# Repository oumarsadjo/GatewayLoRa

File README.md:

# SUIVI COMPLET DU PROJET -> GatewayLoRa
- Annee: 2023-2024
- Projet: GetwayLoRa
- Niveau: 4 annee
- Ecole: Polytch Nice Sophia
- Eleves: Oumar Sadjo Barry & Mor Djeng / oumar-sadjo.barry@etu.univ-cotedazur.fr & mor.dieng@etu.univ-cotedazur.fr
- Professeur: Monsieur Christian Peter / christian.peter@univ-cotedazur.fr
- Derniere mise a jour: _Lundi 05 Fevrier 2024_          

## LES ETAPES QUE NOUS AVONS SUIVI SONT

_1. LECTURES DES DIFFERENTES DOCUMENTATIONS
------------------------------------------
Nous avons commencé par lire attentivement toutes les documents (datasheets),
des deux cartes. C'est qui nous a donne une vue générale de leurs fonctionnements.
Nous avons analysé les differents schematics et prendre connaissance de leur brochages.

_2. INTERCONNEXION DES DEUX CARTES (CABLAGE)
------------------------------------------
Apres avoir pris connaissance des deux datasheet, nous avons choisi un protocole de
communication UART pour permettre la transmission. Nous avons identifié l'alimentation
des deux cartes qui à 5V chacune.

_3. PROTOCOLE ET BROCHAGE
------------------------
- Protocole: UART
- Connexion:
- ESP32 (ports) vers SIM7000G (ports)
- 5V    ------------> V
- GND   ------------> G
- 16    ------------> T //RX to TX
- 17    ------------> R //TX to RX

_4. UTILISATION DE IDE ARDUINO POUR LES TESTS
--------------------------------------------
Nous avons codé une première fonction "void sendCommand(String myCommand)", qui permet
d'envoyer des commandes AT et afficher le resultat au port serial désiré.
NOTE: Toutes les fonctions sont ecrites dans un fichier d'entete (header), nomme "myFonctions.h".

_5. LES PREMIERES FONCTIONS
-------------------------
Nous avons ecris une premiere fonction capable d'envoyer un SMS a un numero désiré nommee : 
"void sendMessage(const char* numero, const char* texte)" et une deuxième fonction qui permet de lire
des messages recus nommee: "void readMessage()".

_6. FONCTIONS PRINCIPALES
------------------------
- A. void myWiFiConnexion(const char* ssid, const char* password): cette fonction nous permet de se connecter un reseau WiFi desire.

- B. void sendRequestByWiFi(const char* ssid, const char* password, const String urlServer):
   Cette fonction permet d'envoyer des requettes HTTP GET en utilisant un reseau WiFi dedié. La limite de cette foncttionnalité,
   est que certains endroits où se projet sera utilisé; n'ont pas de WiFi. Pour aller plus loin, on va utiliser le GSM.
  Elle procede comme suit:
  - a. Connexion a un reseau WiFi
  - b. Verification de la connexion
  - c. Initialisation du protocole HTTP
  - d. Obtention de la longeur ou de la taille de la page
  - e. Affichage du resultat obtenu
  - f. Fermeture du protocole HTTP
    
- C. void sendRequestByGSM(const char* url):
   Cette fonction permet d'envoyer des requettes HTTP GET en utilisant le reseau GSM. L'utilisateur precise le serveur ou le lien.
   Elle procede comme suit:
  - a. Initialisation du reseau GSM
  - b. Obtention d'une IP adress pour communiquer en GSM
  - c. Initialisation du protocole HTTP
  - d. Obtention de la longeur ou de la taille de la page
  - e. Affichage du resultat obtenu
  - f. Fermeture du protocole HTTP

_7. ETAPES SCHEMATICS
--------------------
Pour cette etape de Design, nous avons choisi l'ensemble des composants et voir leur disponibilite sur le site du sous-traitant.
Le design a ete valide par notre professeur. Nous avons constitue le BOM et l'envoye au professeur pour commander les composants.
Nous allons maintenant passer a l'etape de routage.

Lors de la seance du 13 Fevrier 2024, nous avons apporter des corrections au schematic et ajouter le convertisseur TXB0108PWR
pour connecter les tensions de +1V8.

_8. ETAPES ROUTAGE
--------------------
Comme le design a ete valide et les materiels sont disponible, nous allons maintenant continuer le routage...
A continuer lors de la prochaine seance : _Mardi 18 Fevrier 2024_

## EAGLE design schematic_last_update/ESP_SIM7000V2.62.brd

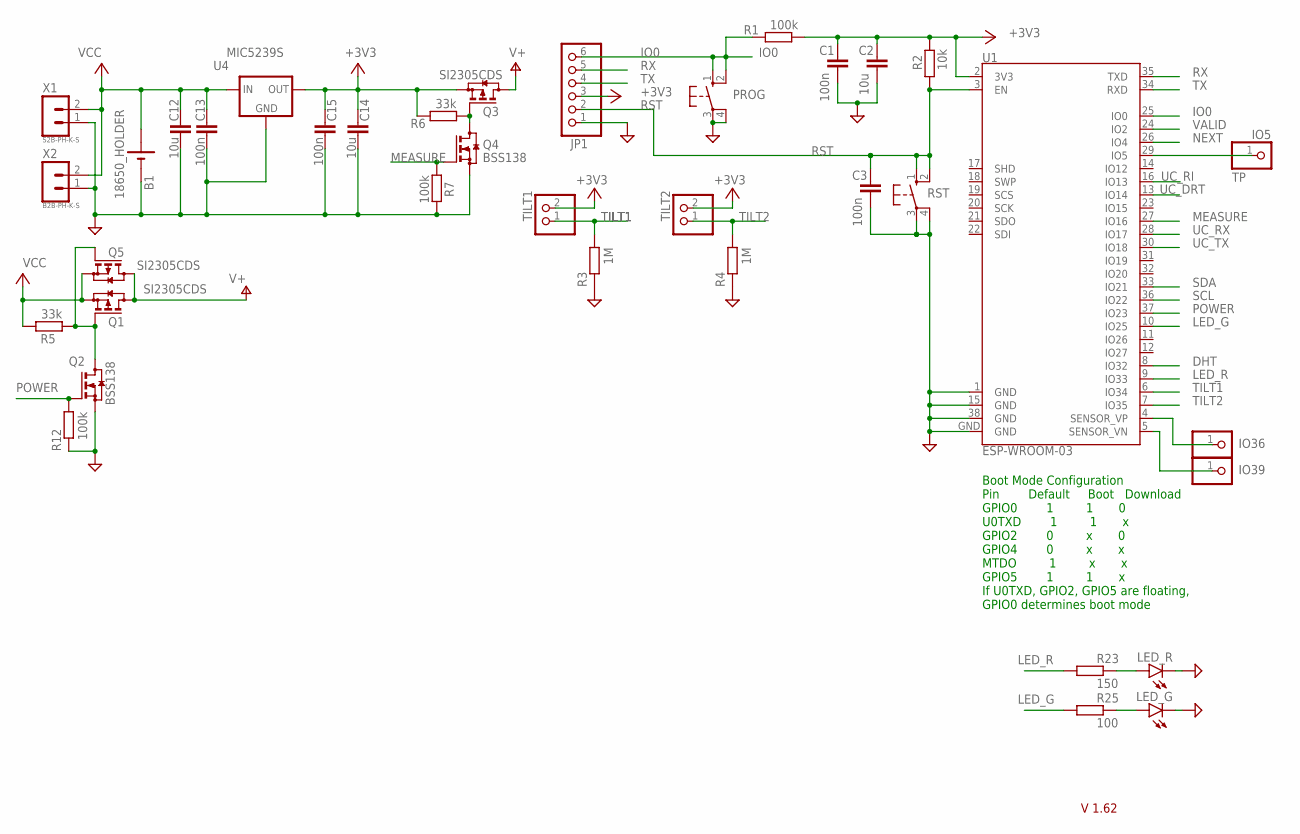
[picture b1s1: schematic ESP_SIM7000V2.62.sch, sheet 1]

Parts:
B1: 18650_HOLDER; 18650
C1, C3, C13, C15: 100n; C1206
C2, C12, C14: 10u; C1210
IO5: TP; 1X01
IO36, IO39: PINHD-1X1; 1X01
JP1: PINHD-1X6; 1X06
LED_G: LEDSMT1206; 1206
LED_R: LEDSMT1206; 1206
PROG: 10-XX; B3F-10XX
Q1, Q3, Q5: SI2305CDS; SOT23
Q2, Q4: BSS138; SOT23
R1, R7, R12: 100k; R1206
R2: 10k; R1206
R3, R4: 1M; R1206
R5, R6: 33k; R1206
R23: 150; R1206
R25: 100; R1206
RST: 10-XX; B3F-10XX
TILT1, TILT2: PINHD-1X2; 1X02
U1: ESP-WROOM-03
U4: MIC5239S; SOT223
X1: S2B-PH-K-S
X2: B2B-PH-K-S

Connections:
+3V3: C1.1, C2.1, C14.1, C15.1, JP1.3, Q3.2 (S), R1.1, R2.2, R6.2, TILT1.2, TILT2.2, U1.2 (3V3), U4.3 (OUT); also elsewhere on the board
DHT: U1.8 (IO32)
GND: B1.-, C1.2, C2.2, C3.2, C12.2, C13.2, C14.2, C15.2, JP1.1, LED_G.C, LED_R.C, PROG.3, PROG.4 (P1), Q2.2 (S), Q4.2 (S), R3.2, R4.2, R7.2, R12.2, RST.3, RST.4 (P1), U1.1 (GND), U1.15 (GND), U1.38 (GND), U1.GND, U4.2 (GND), U4.4 (GND), X1.1, X2.1; also elsewhere on the board
IO0: JP1.6, PROG.1 (S), PROG.2 (S1), R1.2, U1.25 (IO0)
IO36: IO36.1, U1.4 (SENSOR_VP)
IO39: IO39.1, U1.5 (SENSOR_VN)
LED_G: R25.1, U1.10 (IO25)
LED_R: R23.1, U1.9 (IO33); also elsewhere on the board
MEASURE: Q4.1 (G), R7.1, U1.27 (IO16)
unnamed: Q1.1 (G), Q2.3 (D), Q5.1 (G), R5.1
unnamed: Q3.1 (G), Q4.3 (D), R6.1
unnamed: LED_R.A, R23.2
unnamed: LED_G.A, R25.2
unnamed: IO5.1, U1.29 (IO5)
NEXT: U1.26 (IO4)
POWER: Q2.1 (G), R12.1, U1.37 (IO23)
RST: C3.1, JP1.2, R2.1, RST.1 (S), RST.2 (S1), U1.3 (EN)
RX: JP1.5, U1.35 (TXD)
SCL: U1.36 (IO22); also elsewhere on the board
SDA: U1.33 (IO21); also elsewhere on the board
TILT1: R3.1, TILT1.1, U1.6 (IO34)
TILT2: R4.1, TILT2.1, U1.7 (IO35)
TX: JP1.4, U1.34 (RXD)
UC_DRT: U1.13 (IO14); also elsewhere on the board
UC_RI: U1.16 (IO13); also elsewhere on the board
UC_RX: U1.28 (IO17); also elsewhere on the board
UC_TX: U1.30 (IO18); also elsewhere on the board
V+: Q1.3 (D), Q3.3 (D), Q5.3 (D); also elsewhere on the board
VALID: U1.24 (IO2)
VCC: B1.+, C12.1, C13.1, Q1.2 (S), Q5.2 (S), R5.2, U4.1 (IN), X1.2, X2.2

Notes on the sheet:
Boot Mode Configuration Pin Default Boot Download GPIO0 1 1 0 U0TXD 1 1 x GPIO2 0 x 0 GPIO4 0 x x MTDO 1 x x GPIO5 1 1 x If U0TXD, GPIO2, GPIO5 are floating, GPIO0 determines boot mode
V 1.62

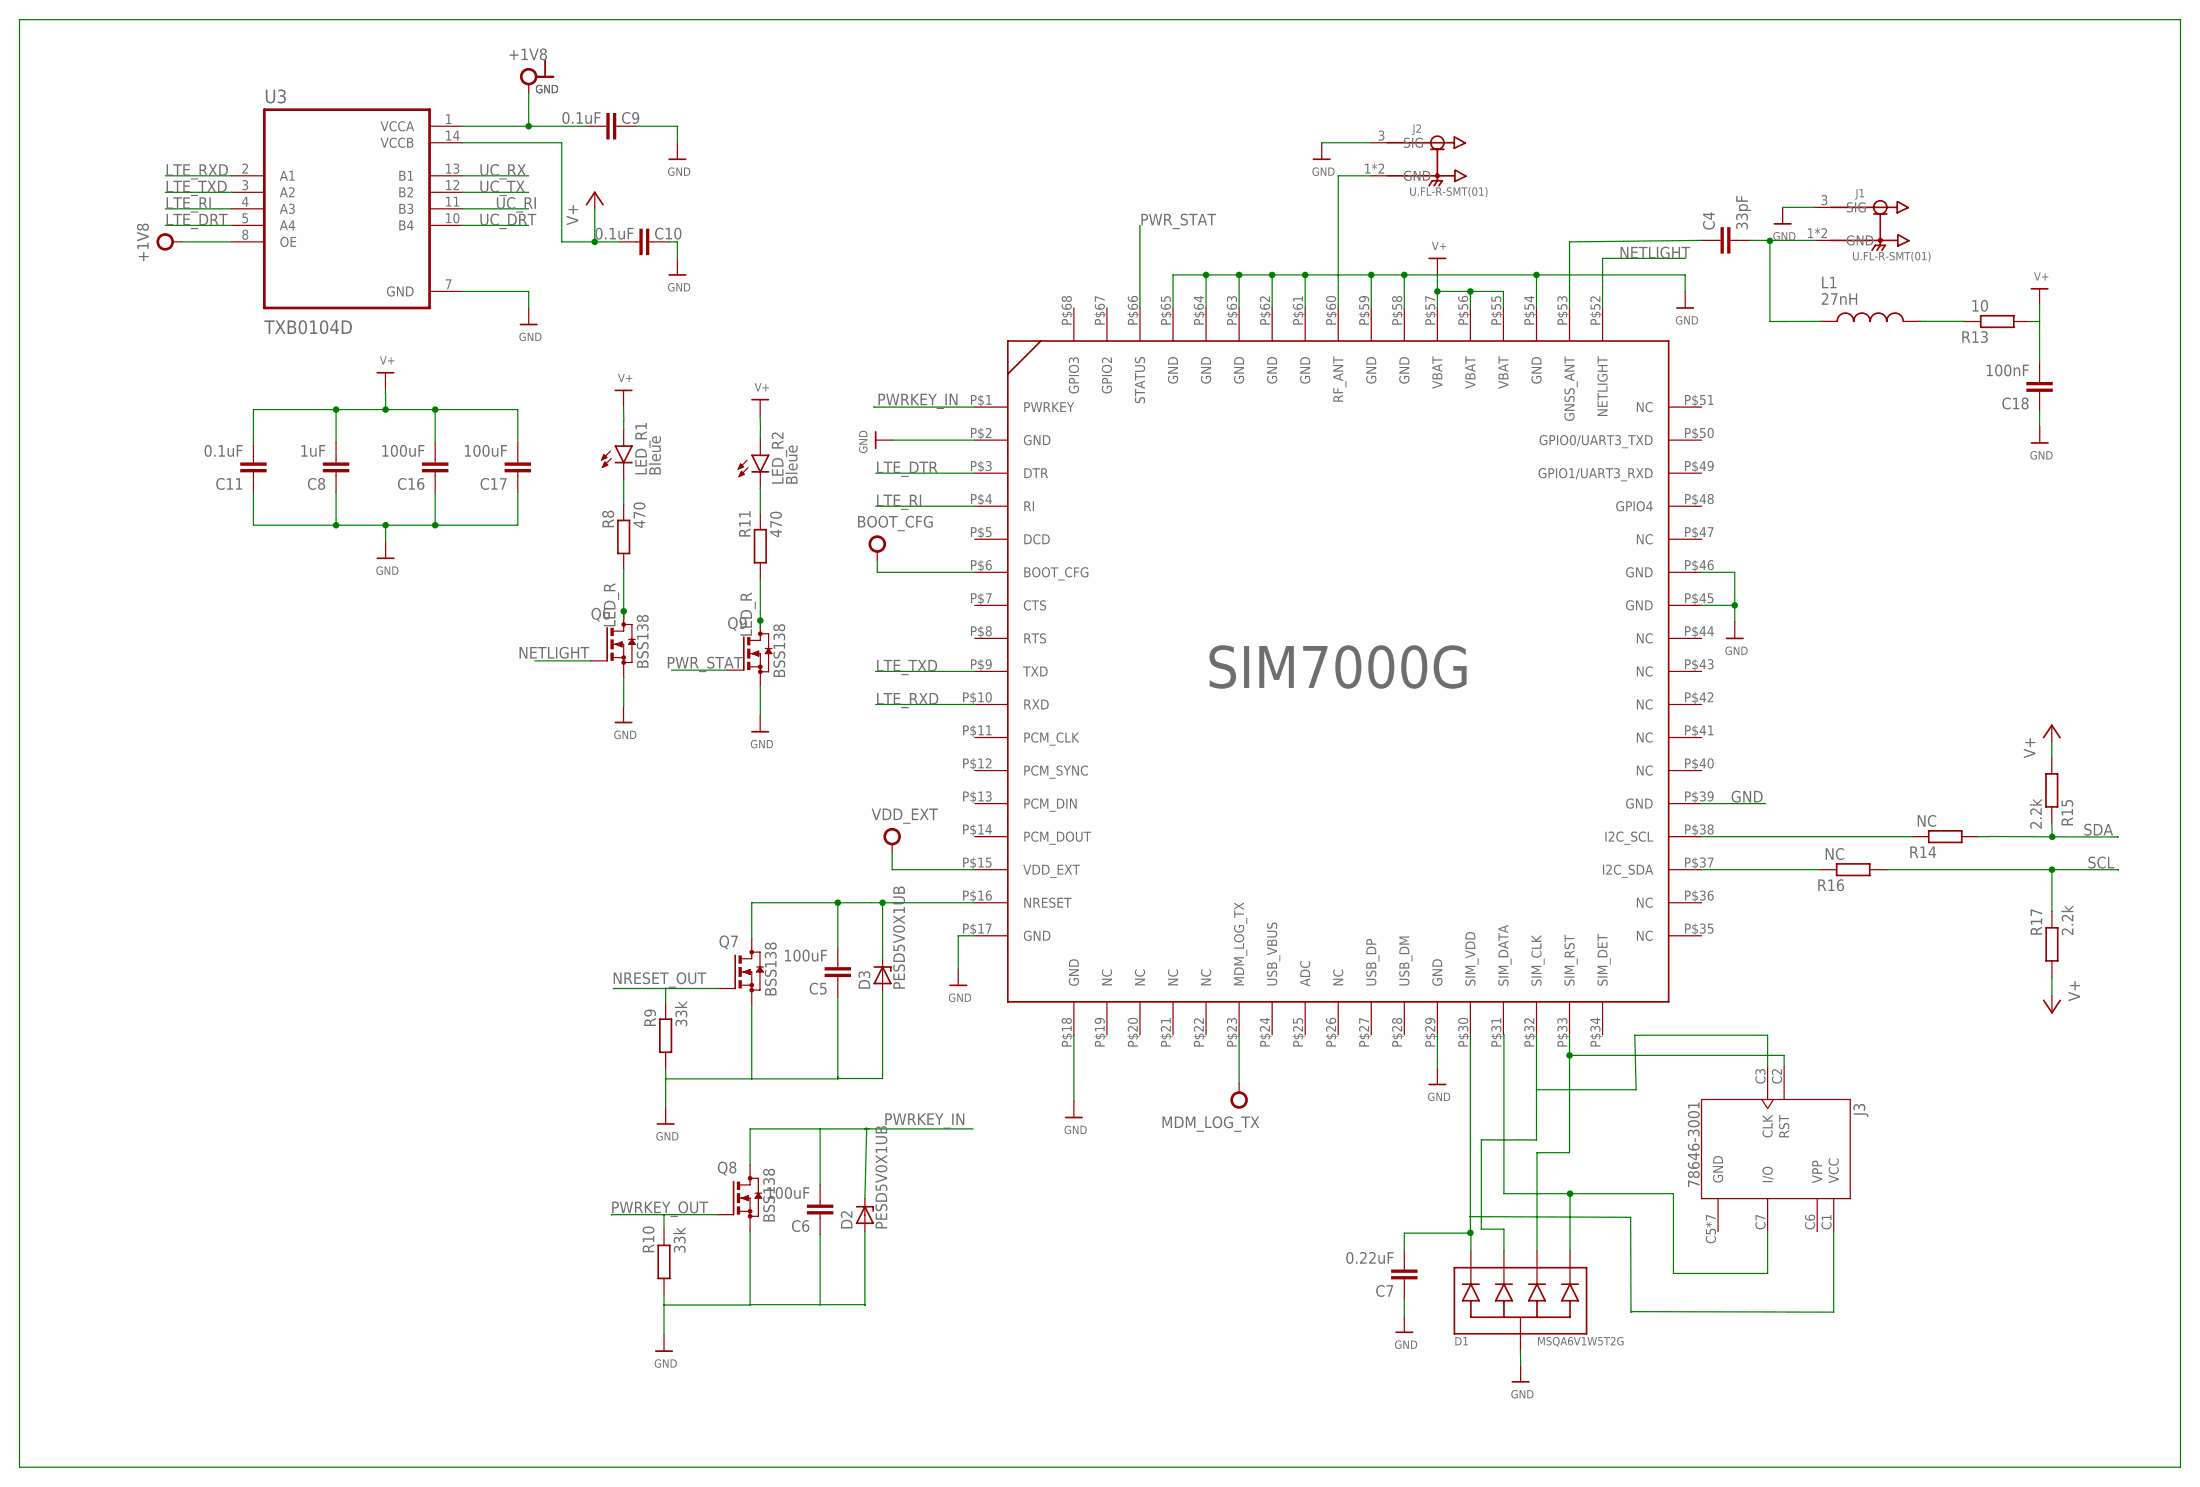
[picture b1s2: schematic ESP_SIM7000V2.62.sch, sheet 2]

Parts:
C4: 33pF; C0805
C5, C6, C16, C17: 100uF; C0805
C7: 0.22uF; C0805
C8: 1uF; C0805
C9, C10: 0.1uF; C1210
C11: 0.1uF; C0805
C18: 100nF; C0805
D1: MSQA6V1W5T2G; SC88A
D2, D3: PESD5V0X1UB; SOD523
J1, J2: U.FL-R-SMT(01); HRS_U.FL-R-SMT(01)
J3: 78646-3001; MOLEX_78646-3001
L1: 27nH; INDC2012X100N
LED_R1, LED_R2: Bleue; 1206
Q6, Q7, Q8, Q9: BSS138; SOT23
R8, R11: 470; R1206
R9, R10: 33k; R1206
R13: 10; R1206
R14, R16: NC; R1206
R15, R17: 2.2k; R1206
U3: TXB0104D; SOIC127P600X175-14N
U$1: SIM7000G

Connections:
+1V8: C9.2, U3.1 (VCCA), U3.8 (OE), U$1.P$6 (BOOT_CFG), U$1.P$15 (VDD_EXT), U$1.P$23 (MDM_LOG_TX)
+3V3: R15.1; also elsewhere on the board
+5V: C10.2, U3.14 (VCCB)
GND: C7.1, C8.1, C9.1, C10.1, C11.1, C16.1, C17.1, C18.1, D1.2, J1.3 (SIG), J2.3 (SIG), J3.C5 (GND), J3.G1 (GND), J3.G2 (GND), J3.G3 (GND), J3.G4 (GND), J3.G5 (GND), J3.G6 (GND), Q6.2 (S), Q9.2 (S), U3.7 (GND), U$1.P$2 (GND), U$1.P$17 (GND), U$1.P$18 (GND), U$1.P$29 (GND), U$1.P$39 (GND), U$1.P$45 (GND), U$1.P$46 (GND), U$1.P$54 (GND), U$1.P$55 (VBAT), U$1.P$56 (VBAT), U$1.P$57 (VBAT), U$1.P$58 (GND), U$1.P$59 (GND), U$1.P$61 (GND), U$1.P$62 (GND), U$1.P$63 (GND), U$1.P$64 (GND), U$1.P$65 (GND); also elsewhere on the board
LED_R: Q6.3 (D), Q9.3 (D), R8.1, R11.1; also elsewhere on the board
LTE_DRT: U3.5 (A4)
LTE_DTR: U$1.P$3 (DTR)
LTE_RI: U3.4 (A3), U$1.P$4 (RI)
LTE_RXD: U3.2 (A1), U$1.P$10 (RXD)
LTE_TXD: U3.3 (A2), U$1.P$9 (TXD)
unnamed: J2.1 (GND), J2.2 (GND), U$1.P$60 (RF_ANT)
unnamed: C4.2, J1.1 (GND), J1.2 (GND), L1.1
unnamed: C4.1, U$1.P$53 (GNSS_ANT)
unnamed: C5.2, D3.1 (K), Q7.3 (D), U$1.P$16 (NRESET)
unnamed: LED_R1.C, R8.2
unnamed: D1.5, J3.C7 (I/O), U$1.P$31 (SIM_DATA)
unnamed: D1.4, J3.C2 (RST), U$1.P$33 (SIM_RST)
unnamed: C8.2, C11.2, C16.2, C17.2
unnamed: Q7.2 (S), R9.1
unnamed: Q8.2 (S), R10.1
unnamed: LED_R2.C, R11.2
unnamed: C18.2, R13.1
unnamed: L1.2, R13.2
unnamed: D1.3, U$1.P$32 (SIM_CLK)
unnamed: R14.2, U$1.P$38 (I2C_SCL)
unnamed: R16.2, U$1.P$37 (I2C_SDA)
unnamed: C7.2, D1.1, U$1.P$30 (SIM_VDD)
NETLIGHT: Q6.1 (G), U$1.P$52 (NETLIGHT)
NRESET_OUT: Q7.1 (G)
PWRKEY_IN: Q8.3 (D), U$1.P$1 (PWRKEY)
PWRKEY_OUT: Q8.1 (G)
PWR_STAT: Q9.1 (G), U$1.P$66 (STATUS)
SCL: R16.1, R17.2; also elsewhere on the board
SDA: R14.1, R15.2; also elsewhere on the board
UC_DRT: U3.10 (B4); also elsewhere on the board
UC_RI: U3.11 (B3); also elsewhere on the board
UC_RX: U3.13 (B1); also elsewhere on the board
UC_TX: U3.12 (B2); also elsewhere on the board
V+: R17.1; also elsewhere on the board
VPP: J3.C6 (VPP)

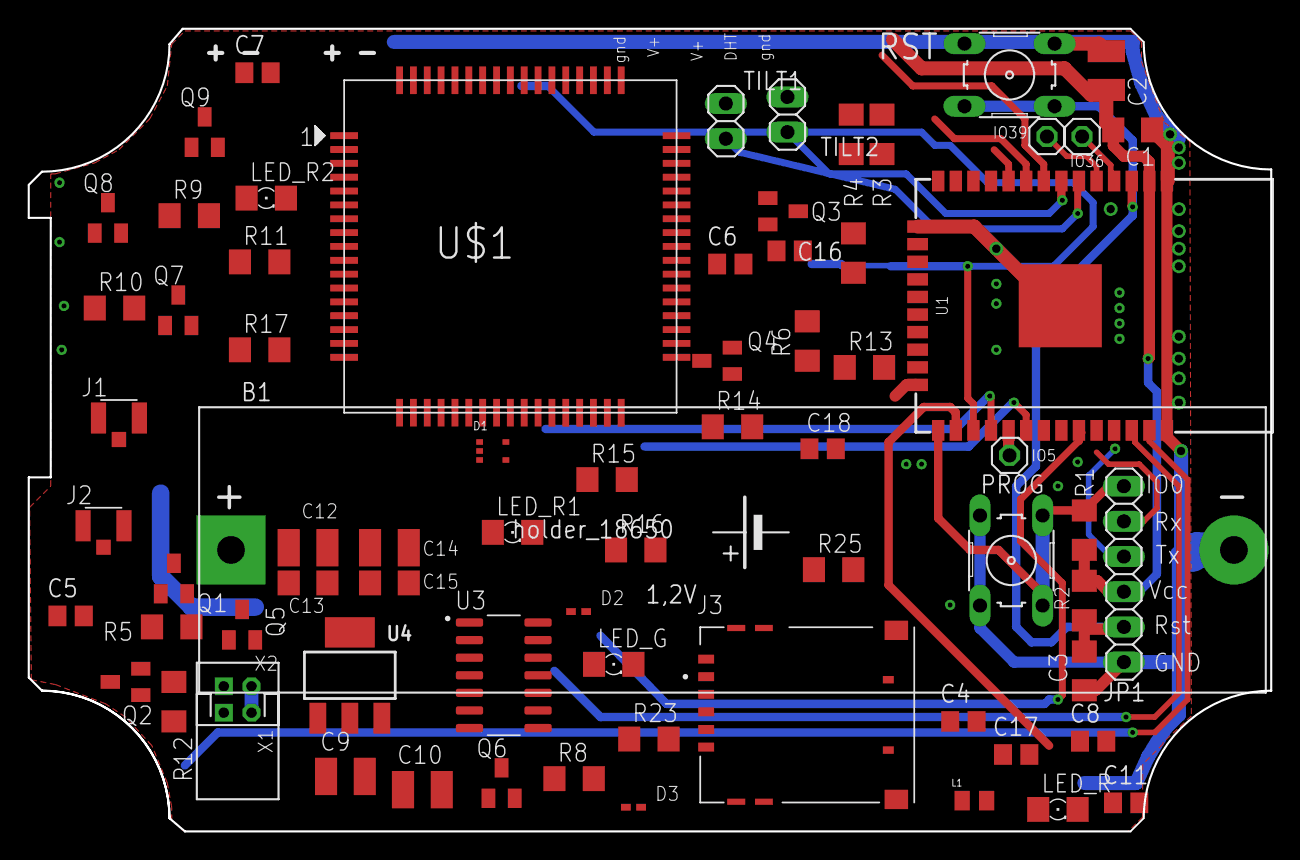
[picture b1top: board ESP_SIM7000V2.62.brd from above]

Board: 2 copper layers, 89.7 x 57.9 mm, 72 parts (0 on the bottom side), 52 nets.

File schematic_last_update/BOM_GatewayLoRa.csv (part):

N°,Type,Part,Value,Device,Package,Needed,Reference,Code commande,SBC,Description,CHECK_PRICES,DESCRIPTION2,DIGIKEY_PART_NUMBER,MF,MP,MPN,OC_FARNELL,OC_NEWARK,PACKAGE3,POPULARITY,PRICE,PURCHASE-URL,RS_COMPONENTS_7092778P_PURCHASE_URL,RS_COMPONENTS_7092778_PURCHASE_URL,RS_COMPONENTS_9236790_PURCHASE_URL,SNAPEDA_LINK,SPICEMODEL,SPICEPREFIX,B1,18650_HOLDER,,,,,,,,,,,,,,,,,,,,C1,100n,CC1206,C1206,"CAPACITOR, European symbol",,,,,,,,,,,,,,,,,,NONE,C,C2,10u,CC1210,C1210,"CAPACITOR, European symbol",,,,,,,,,,,,,,,,,,NONE,C,C3,100n,CC1206,C1206,"CAPACITOR, European symbol",,,,,,,,,,,,,,,,,,NONE,C,C4,33pF,C-EUC0805,C0805,"CAPACITOR, European symbol",,,,,,,,,,,88,,,,,,,,C,C5,100uF,C-EUC0805,C0805,"CAPACITOR, European symbol",,,,,,,,,,,88,,,,,,,,C,C6,100uF,C-EUC0805,C0805,"CAPACITOR, European symbol",,,,,,,,,,,88,,,,,,,,C,C7,0.22uF,C-EUC0805,C0805,"CAPACITOR, European symbol",,,,,,,,,,,88,,,,,,,,C,C8,1uF,C-EUC0805,C0805,"CAPACITOR, European symbol",,,,,,,,,,,88,,,,,,,,C,C9,0.1uF,CC1210,C1210,"CAPACITOR, European symbol",,,,,,,,,,,,,,,,,,NONE,C,C10,0.1uF,CC1210,C1210,"CAPACITOR, European symbol",,,,,,,,,,,,,,,,,,NONE,C,C11,0.1uF,C-EUC0805,C0805,"CAPACITOR, European symbol",,,,,,,,,,,88,,,,,,,,C,C12,10u,CC1210,C1210,"CAPACITOR, European symbol",,,,,,,,,,,,,,,,,,NONE,C,C13,100n,CC1206,C1206,"CAPACITOR, European symbol",,,,,,,,,,,,,,,,,,NONE,C,C14,10u,CC1210,C1210,"CAPACITOR, European symbol",,,,,,,,,,,,,,,,,,NONE,C,C15,100n,CC1206,C1206,"CAPACITOR, European symbol",,,,,,,,,,,,,,,,,,NONE,C,C16,100uF,C-EUC0805,C0805,"CAPACITOR, European symbol",,,,,,,,,,,88,,,,,,,,C,C17,100uF,C-EUC0805,C0805,"CAPACITOR, European symbol",,,,,,,,,,,88,,,,,,,,C,C18,100nF,C-EUC0805,C0805,"CAPACITOR, European symbol",,,,,,,,,,,88,,,,,,,,C,D1,MSQA6V1W5T2G,MSQA6V1W5T2G,SC88A,ESD Protection Diode Array  Check availability,In Stock,https://www.snapeda.com/parts/MSQA6V1W5T2G/Onsemi/view-part/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,Clamp Ipp Tvs Diode Surface Mount SC-88A (SC-70-5/SOT-353),,onsemi,MSQA6V1W5T2G,,,,SC-88A-5 ON Semiconductor,,None,https://www.snapeda.com/api/url_track_click_mouser/?unipart_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,,,,https://www.snapeda.com/parts/MSQA6V1W5T2G/Onsemi/view-part/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,,,D2,PESD5V0X1UB,PESD5V0X1UB,SOD523,Ultra low capacitance unidirectional ElectroStatic Discharge (ESD) protection diode in a,In Stock,https://www.snapeda.com/parts/PESD5V0X1UB/Nexperia/view-part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,8V (Typ) Clamp 1.5A (8/20Âµs) Ipp Tvs Diode Surface Mount SOD-523,,Nexperia USA,PESD5V0X1UB,,,,SOD-523 NXP Semiconductors,,None,,,,,https://www.snapeda.com/parts/PESD5V0X1UB/Nexperia/view-part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,,,D3,PESD5V0X1UB,PESD5V0X1UB,SOD523,Ultra low capacitance unidirectional ElectroStatic Discharge (ESD) protection diode in a,In Stock,https://www.snapeda.com/parts/PESD5V0X1UB/Nexperia/view-part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,8V (Typ) Clamp 1.5A (8/20Âµs) Ipp Tvs Diode Surface Mount SOD-523,,Nexperia USA,PESD5V0X1UB,,,,SOD-523 NXP Semiconductors,,None,,,,,https://www.snapeda.com/parts/PESD5V0X1UB/Nexperia/view-part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,,,IO5,TP,PINHD-1X1,1X01,PIN HEADER,,,,,,,,,,,64,,,,,,,,,IO36,,PINHD-1X1,1X01,PIN HEADER,,,,,,,,,,,64,,,,,,,,,IO39,,PINHD-1X1,1X01,PIN HEADER,,,,,,,,,,,64,,,,,,,,,J1,U.FL-R-SMT(01),U.FL-R-SMT(01),HRS_U.FL-R-SMT(01),U.FL Series 6 Ghz 50 Ohm Ultra-small SMT Coaxial Cable Receptacle Check availability,In Stock,https://www.snapeda.com/parts/U.FL-R-SMT(01)/Hirose+Electric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,"U.FL (UMCC) Connector Receptacle, Male Pin 50Ohm Surface Mount Solder. RF Connectors / Coaxial Connectors",,Hirose,U.FL-R-SMT(01),,,,None,,None,https://www.snapeda.com/api/url_track_click_mouser/?unipart_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,,,,https://www.snapeda.com/parts/U.FL-R-SMT(01)/Hirose+Electric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,,,J2,U.FL-R-SMT(01),U.FL-R-SMT(01),HRS_U.FL-R-SMT(01),U.FL Series 6 Ghz 50 Ohm Ultra-small SMT Coaxial Cable Receptacle Check availability,In Stock,https://www.snapeda.com/parts/U.FL-R-SMT(01)/Hirose+Electric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,"U.FL (UMCC) Connector Receptacle, Male Pin 50Ohm Surface Mount Solder. RF Connectors / Coaxial Connectors",,Hirose,U.FL-R-SMT(01),,,,None,,None,https://www.snapeda.com/api/url_track_click_mouser/?unipart_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,,,,https://www.snapeda.com/parts/U.FL-R-SMT(01)/Hirose+Electric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,,,JP1,,PINHD-1X6,1X06,PIN HEADER,,,,,,,,,,,79,,,,,,,,,L,27nH,L-LQH55,LQH55,,,,,,,,,,,,,,,,,,,,,LED_G,,LEDSMT1206,1206,LED,,,,,,,,,,,20,,,,,,,,,LED_R,,LEDSMT1206,1206,LED,,,,,,,,,,,20,,,,,,,,,LED_R1,Bleue,LEDSMT1206,1206,LED,,,,,,,,,,,20,,,,,,,,,LED_R2,Bleue,LEDSMT1206,1206,LED,,,,,,,,,,,20,,,,,,,,,PROG,,10-XX,B3F-10XX,OMRON SWITCH,,,,,,,B3F-1000,176432,36M3542,,72,,,,,,,,,Q1,SI2305CDS,SI2305CDS,SOT23,P-CHANNEL MOS FET,,,,,,,,,,,,,,,,,,,,Q2,BSS138,BSS131,SOT23,N-CHANNEL MOS FET,,,,,,,,,,,,,,,,,,,,Q3,SI2305CDS,SI2305CDS,SOT23,P-CHANNEL MOS FET,,,,,,,,,,,,,,,,,,,,Q4,BSS131,BSS131,SOT23,N-CHANNEL MOS FET,,,,,,,,,,,,,,,,,,,,Q5,SI2305CDS,SI2305CDS,SOT23,P-CHANNEL MOS FET,,,,,,,,,,,,,,,,,,,,Q6,BSS138,BSS131,SOT23,N-CHANNEL MOS FET,,,,,,,,,,,,,,,,,,,,Q7,BSS138,BSS131,SOT23,N-CHANNEL MOS FET,,,,,,,,,,,,,,,,,,,,Q8,BSS138,BSS131,SOT23,N-CHANNEL MOS FET,,,,,,,,,,,,,,,,,,,,Q9,BSS138,BSS131,SOT23,N-CHANNEL MOS FET,,,,,,,,,,,,,,,,,,,,R1,100k,RR1206,R1206,"RESISTOR, European symbol",,,,,,,,,,,,,,,,,,NONE,R,R2,10k,RR1206,R1206,"RESISTOR, European symbol",,,,,,,,,,,,,,,,,,NONE,R,R3,1M,RR1206,R1206,"RESISTOR, European symbol",,,,,,,,,,,,,,,,,,NONE,R,R4,1M,RR1206,R1206,"RESISTOR, European symbol",,,,,,,,,,,,,,,,,,NONE,R,R5,33k,RR1206,R1206,"RESISTOR, European symbol",,,,,,,,,,,,,,,,,,NONE,R,R6,33k,RR1206,R1206,"RESISTOR, European symbol",,,,,,,,,,,,,,,,,,NONE,R,R7,100k,RR1206,R1206,"RESISTOR, European symbol",,,,,,,,,,,,,,,,,,NONE,R,R8,470,RR1206,R1206,"RESISTOR, European symbol",,,,,,,,,,,,,,,,,,NONE,R,R9,33k,RR1206,R1206,"RESISTOR, European symbol",,,,,,,,,,,,,,,,,,NONE,R,R10,33k,RR1206,R1206,"RESISTOR, European symbol",,,,,,,,,,,,,,,,,,NONE,R,R11,470,RR1206,R1206,"RESISTOR, European symbol",,,,,,,,,,,,,,,,,,NONE,R,R12,100k,RR1206,R1206,"RESISTOR, European symbol",,,,,,,,,,,,,,,,,,NONE,R,R13,10,RR1206,R1206,"RESISTOR, European symbol",,,,,,,,,,,,,,,,,,NONE,R,R14,NC,RR1206,R1206,"RESISTOR, European symbol",,,,,,,,,,,,,,,,,,NONE,R,R15,2.2k,RR1206,R1206,"RESISTOR, European symbol",,,,,,,,,,,,,,,,,,NONE,R,R16,NC,RR1206,R1206,"RESISTOR, European symbol",,,,,,,,,,,,,,,,,,NONE,R,R17,2.2k,RR1206,R1206,"RESISTOR, European symbol",,,,,,,,,,,,,,,,,,NONE,R,R23,150,RR1206,R1206,"RESISTOR, European symbol",,,,,,,,,,,,,,,,,,NONE,R,R25,100,RR1206,R1206,"RESISTOR, European symbol",,,,,,,,,,,,,,,,,,NONE,R,RST,,10-XX,B3F-10XX,OMRON SWITCH,,,,,,,B3F-1000,176432,36M3542,,72,,,,,,,,,TILT1,,PINHD-1X2,1X02,PIN HEADER,,,,,,,,,,,98,,,,,,,,,TILT2,,PINHD-1X2,1X02,PIN HEADER,,,,,,,,,,,98,,,,,,,,,U$1,SIM7000G,SIM7000G,SIM7000G,,,https://www.snapeda.com/parts/SIM7000G/SIMCom/view-part/?ref=eda,"802.15.4 Cat-M, Cat-NB, EDGE, GPRS, LPWA Transceiver Module 850MHz, 900MHz, 1.8GHz, 1.9GHz Antenna Not Included Surface Mount",,SIMCom Wireless Solutions Limited,SIM7000G,,,,None,,,https://www.snapeda.com/api/url_track_click_mouser/?unipart_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 Wireless Solutions Limitedâ_name=SIM7000G&search_term=sim7000g,,,,https://www.snapeda.com/parts/SIM7000G/SIMCom/view-part/?ref=snap,,,U$2,SCU-W0822XR-06,SCU-W0822XR-06,SCU-W0822XR-06,,,,,,,,,,,,,,,,,,,,,U1,ESP-WROOM-03,ESP-WROOM-03,ESP-WROOM-03,,,,,,,,,unknown,,,,,,,,,,,,U3,TXB0104D,TXB0104D,SOIC127P600X175-14N,,,https://www.snapeda.com/parts/TXB0104D/Texas+Instruments/vie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,4-Bit Bidirectional Voltage-Level Shifter with Auto Direction Sensing and +/-15 kV ESD Protect,,Texas Instruments,TXB0104D,,,,SOIC-14 Texas Instruments,,,https://www.snapeda.com/api/url_track_click_mouser/?unipart_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 Instrumentsâ_name=TXB0104D&search_term=txb0104,https://www.snapeda.com/api/url_track_click/https%253A//uk.r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 Instrumentsâ_name=TXB0104D&search_term=txb0104,https://www.snapeda.com/api/url_track_click/https%253A//uk.r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 Instrumentsâ_name=TXB0104D&search_term=txb0104,https://www.snapeda.com/api/url_track_click/https%253A//uk.r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 Instrumentsâ_name=TXB0104D&search_term=txb0104,https://www.snapeda.com/parts/TXB0104D/Texas+Instruments/vie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,,,U4,MIC5239S,MIC5239S,SOT223,LDO REGULATOR,,,,,,,,,,,,,,,,,,,,X1,S2B-PH-K-S,S2B-PH-K-S,S2B-PH-K
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
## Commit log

2023-10-27 Add schematic v1
2023-10-27 Add brd file
2023-10-27 Ajout de la documentation
2023-11-03 Mise a jour de la fonction sendCommand
2023-11-06 Ajout du travail effectue le 06/11/2023
2023-11-27 Mise a jour du schematic du: 20/11/2023
2024-02-05 Fin du shematic et debut du routage
2024-02-05 Rename README.txt to README.md
    Fin du shematic et debut du routage
2024-02-13 Ajout d'extraction de donnees GPS
2024-02-14 Correction schematic et ajout de TXB0108PWR
2024-02-14 Update README.md
    Correction schematic et ajout de TXB0108PWR
2024-03-22 Ajout du GatewayLoRa - Design - All files

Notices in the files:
parts and their libraries:
micrel: Copyright (C) 2008, Bob Starr
